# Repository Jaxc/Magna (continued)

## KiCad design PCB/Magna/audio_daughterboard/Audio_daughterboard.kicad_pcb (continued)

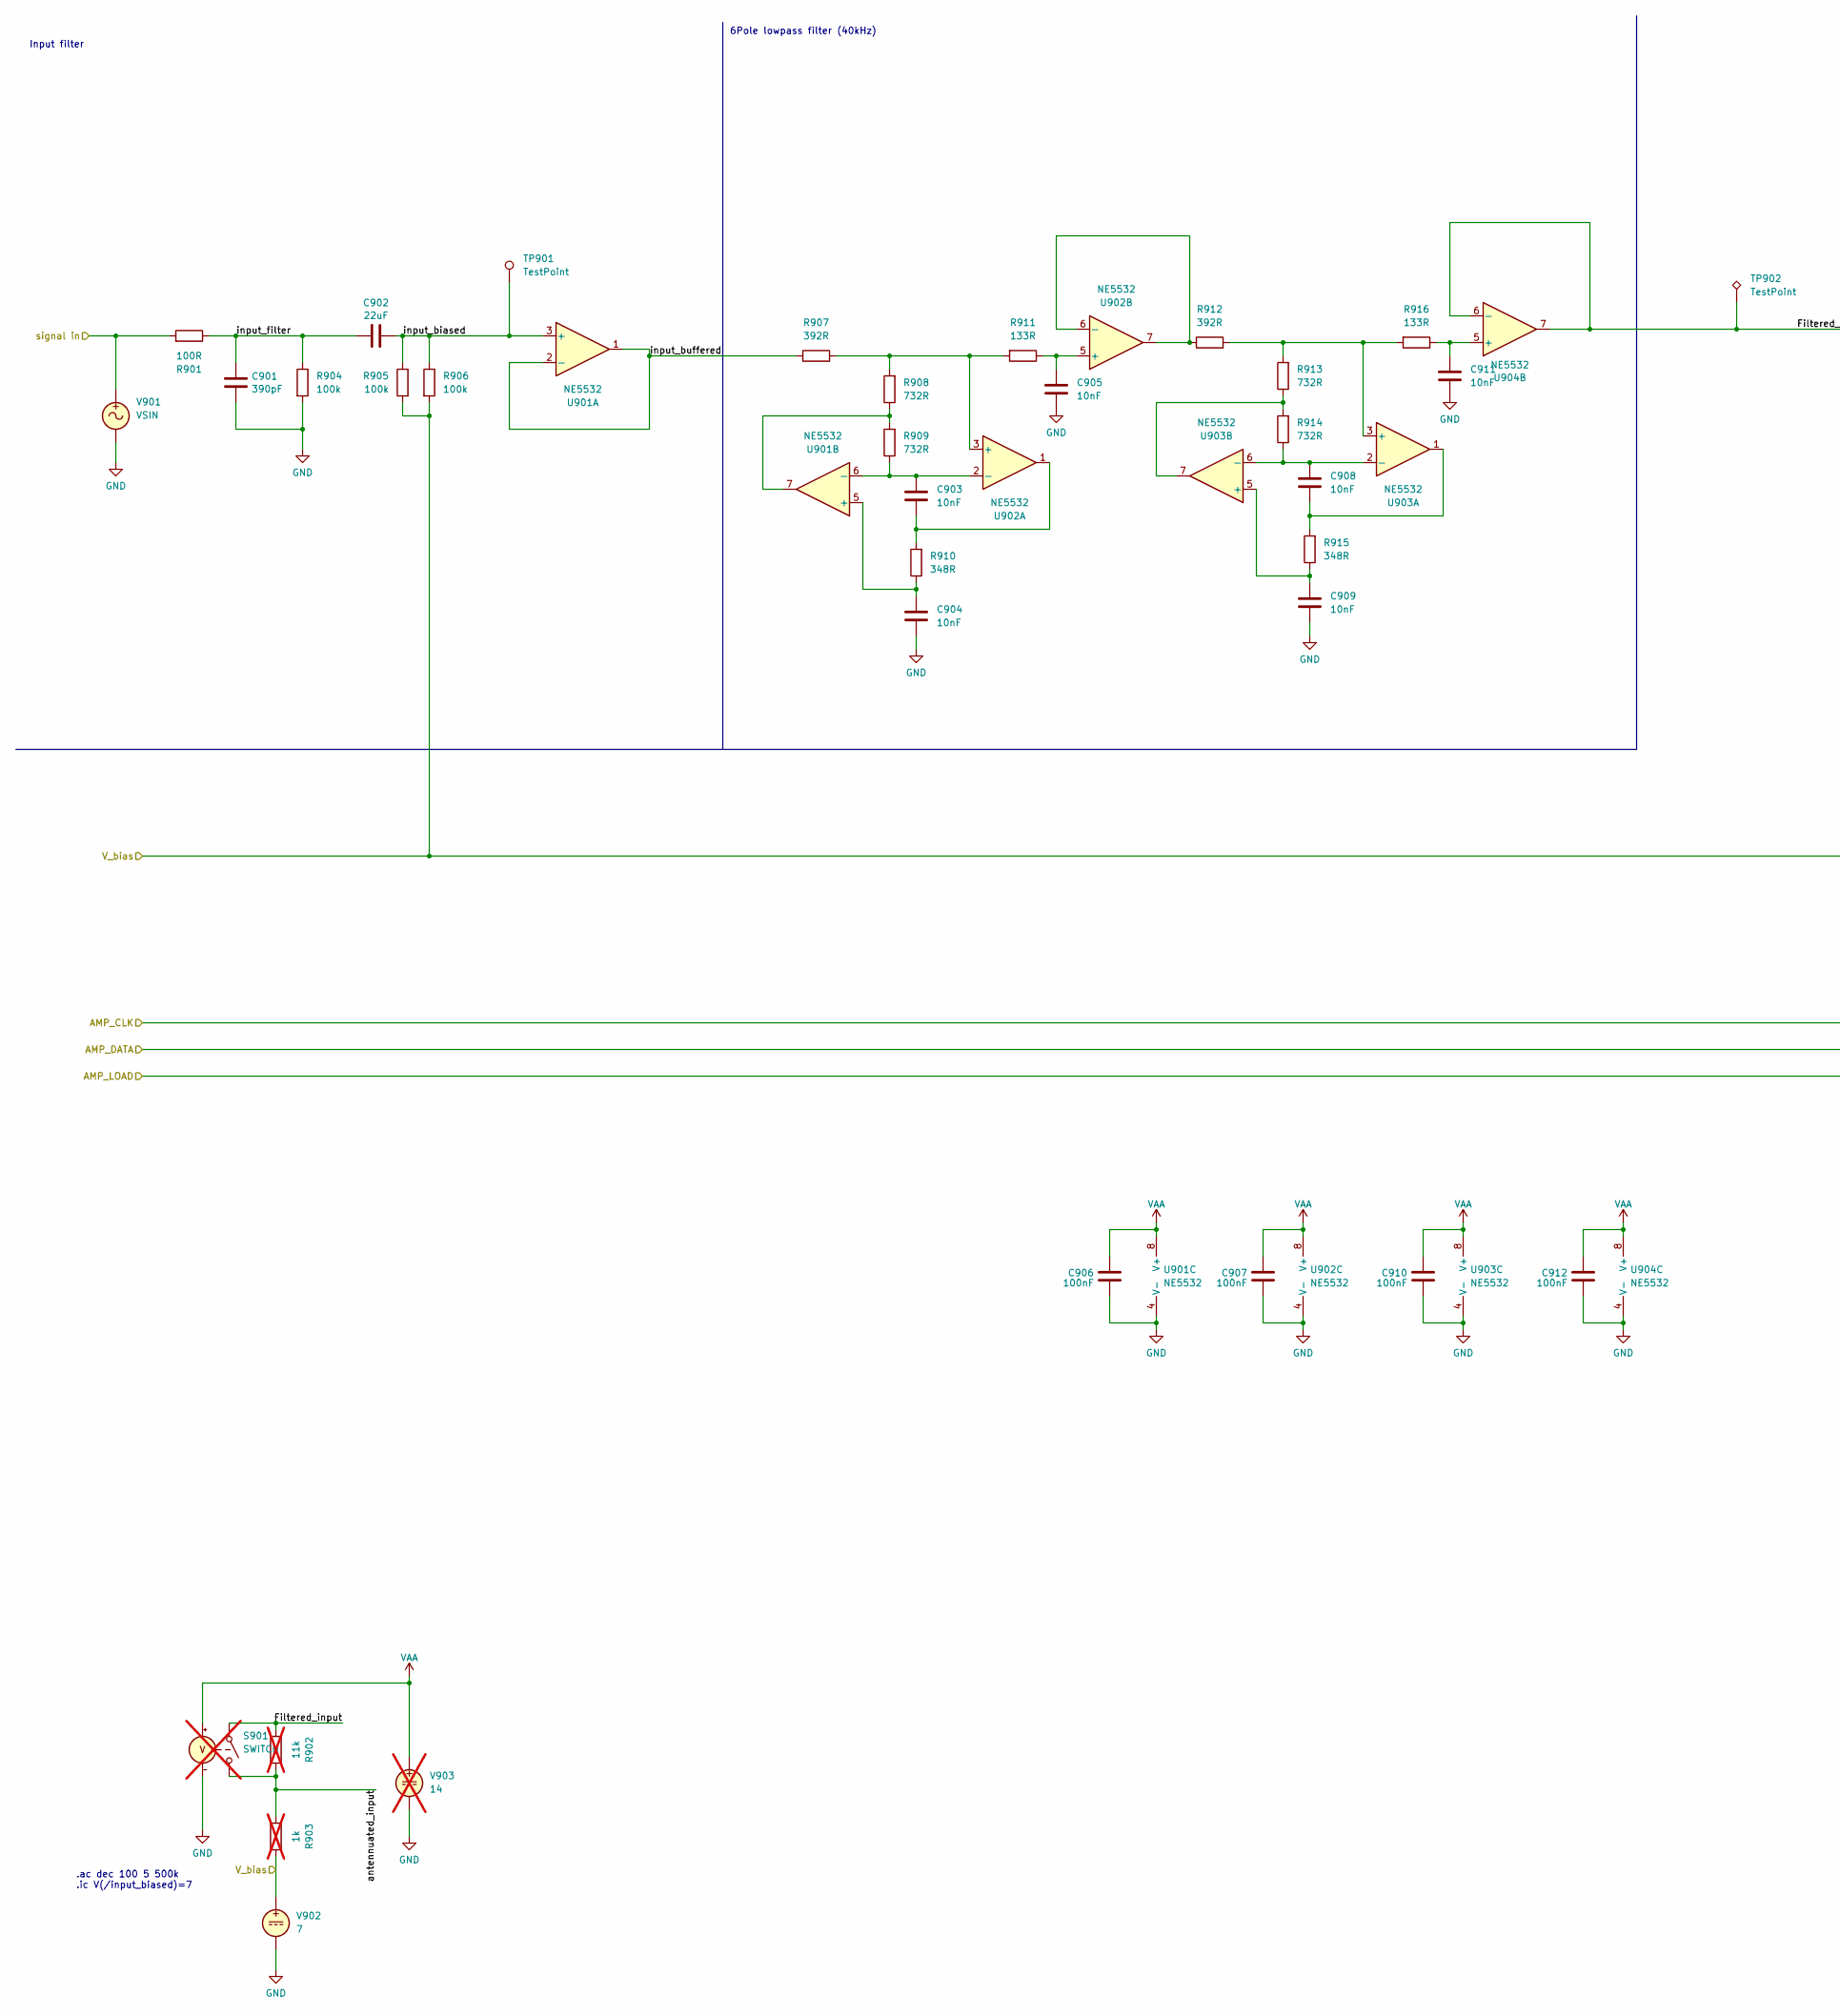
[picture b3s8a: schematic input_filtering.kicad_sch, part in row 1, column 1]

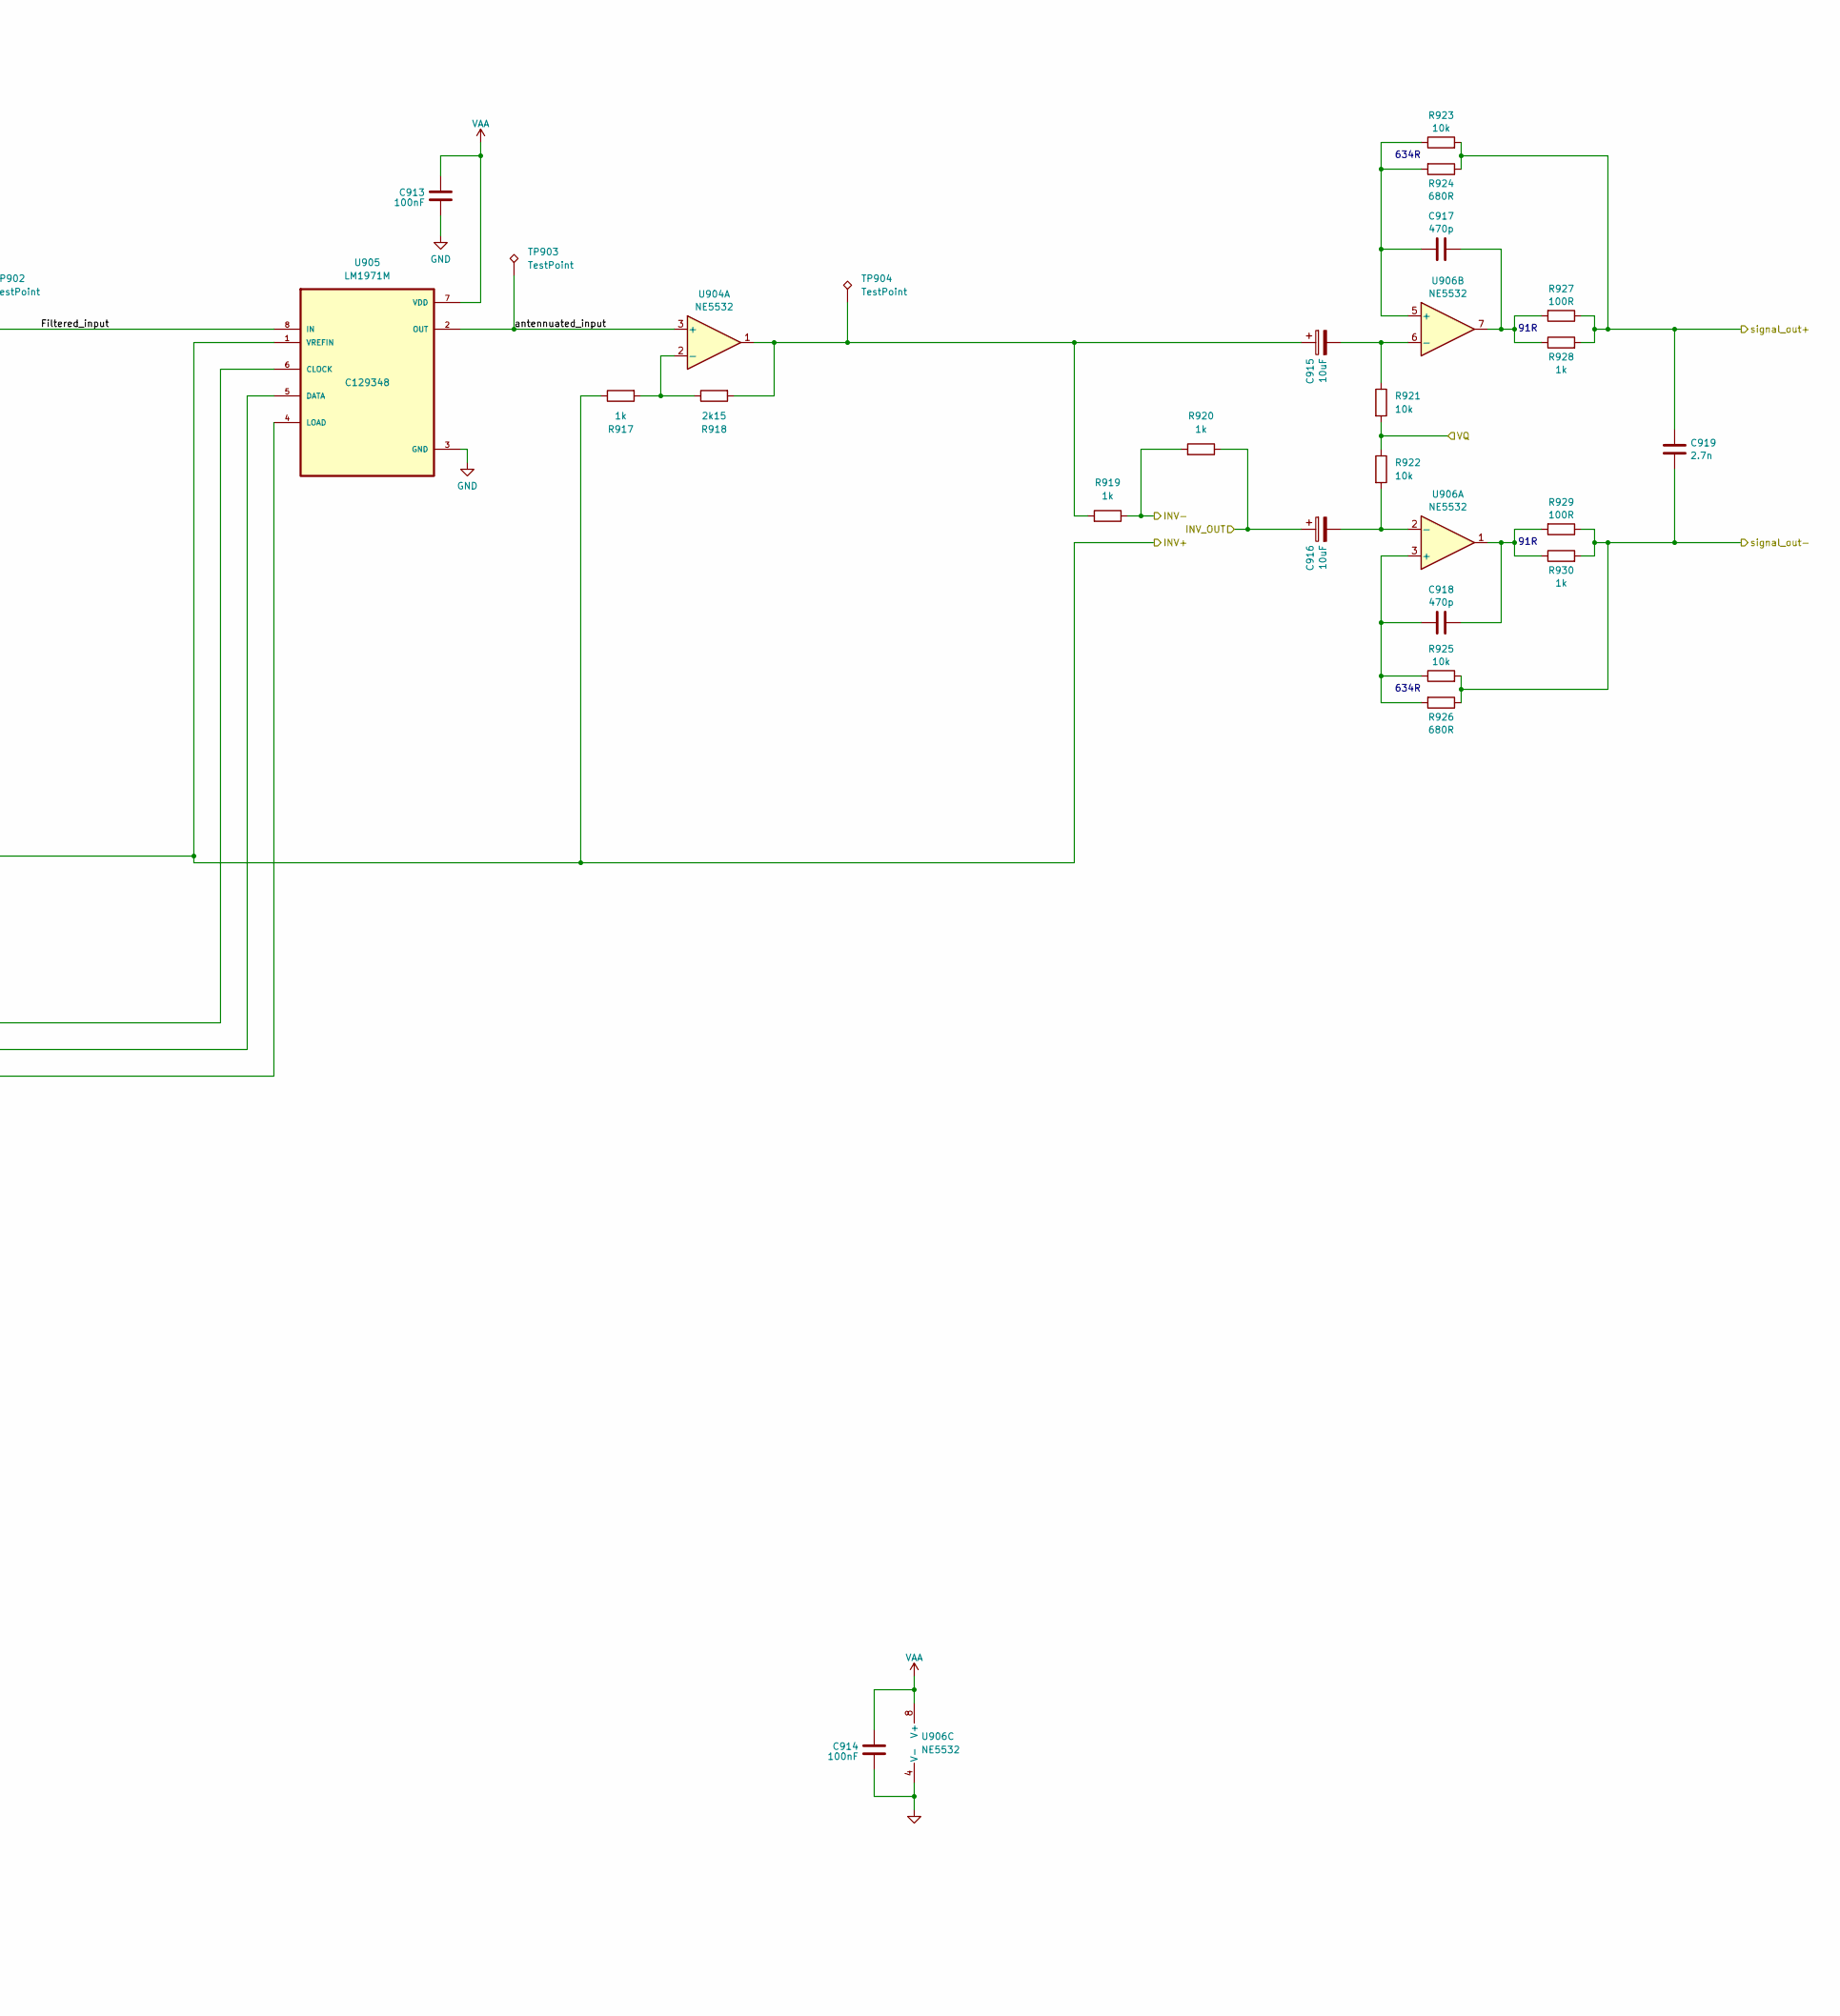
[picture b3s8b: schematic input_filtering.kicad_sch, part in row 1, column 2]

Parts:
C901: 390pF; C_0603_1608Metric; LCSC C472793
C902: 22uF; CP_Elec_6.3x5.4; LCSC C2164172
C903, C904, C905, C908, C909, C911: 10nF; C_0603_1608Metric; LCSC C84709
C906, C907, C910, C912, C913: 100nF; C_0603_1608Metric; Voltage 50V; LCSC C14663
C914: 100nF; C_0603_1608Metric; LCSC C14663
C915, C916: 10uF; CP_Elec_4x5.8; LCSC C2163094
C917, C918: 470p; C_0603_1608Metric; LCSC C27694
C919: 2.7n; C_0603_1608Metric; LCSC C77034
R901, R927, R929: 100R; R_0603_1608Metric; LCSC C122970
R902: 11k; not fitted
R903: 1k; not fitted
R904, R905, R906: 100k; R_0603_1608Metric; LCSC C25803
R907, R912: 392R; R_0603_1608Metric; LCSC C861870
R908, R909, R913, R914: 732R; R_0603_1608Metric; LCSC C861547
R910, R915: 348R; R_0603_1608Metric; LCSC C861337
R911, R916: 133R; R_0603_1608Metric; LCSC C861112
R917, R919, R920, R928, R930: 1k; R_0603_1608Metric; LCSC C110776
R918: 2k15; R_0603_1608Metric; LCSC C667562
R921, R922, R923, R925: 10k; R_0603_1608Metric; LCSC C95204
R924, R926: 680R; R_0603_1608Metric; LCSC C2989042
S901: SWITCH; not fitted
TP901: TestPoint; TestPoint_Keystone_5005-5009_Compact
TP902, TP903, TP904: TestPoint; TestPoint_Pad_1.0x1.0mm
U901, U902, U903, U904, U906: NE5532; SOIC-8_3.9x4.9mm_P1.27mm; LCSC C7426
U905: LM1971M; SOIC-8_3.9x4.9mm_P1.27mm; LCSC C129348
V901: VSIN
V902: 7
V903: 14; not fitted

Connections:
/AudioAdc0/AMP_CLK: U905.6 (CLOCK); also elsewhere on the board
/AudioAdc0/AMP_DATA: U905.5 (DATA); also elsewhere on the board
/AudioAdc0/AMP_LOAD: U905.4 (LOAD); also elsewhere on the board
/AudioAdc0/Input Filtering/Filtered_input: TP902.1, U904.6 (-), U904.7, U905.8 (IN)
/AudioAdc0/Input Filtering/INV-: R919.1, R920.2; also elsewhere on the board
/AudioAdc0/Input Filtering/INV_OUT: C916.1, R920.1; also elsewhere on the board
/AudioAdc0/Input Filtering/antennuated_input: TP903.1, U904.3 (+), U905.2 (OUT)
/AudioAdc0/Input Filtering/input_biased: C902.1, R905.1, R906.1, TP901.1, U901.3 (+)
/AudioAdc0/Input Filtering/input_buffered: R907.1, U901.1, U901.2 (-)
/AudioAdc0/Input Filtering/input_filter: C901.2, C902.2, R901.1, R904.1
/AudioAdc0/Input Filtering/signal in: R901.2; also elsewhere on the board
/AudioAdc0/Input Filtering/signal_out+: C919.1, R923.2, R924.1, R927.1, R928.2; also elsewhere on the board
/AudioAdc0/Input Filtering/signal_out-: C919.2, R925.2, R926.1, R929.1, R930.2; also elsewhere on the board
/AudioAdc0/VQ: R921.2, R922.1; also elsewhere on the board
GND: C901.1, C904.2, C905.2, C906.2, C907.2, C909.2, C910.2, C911.2, C912.2, C913.2, C914.2, R904.2, S901.4 (C-), U901.4 (V-), U902.4 (V-), U903.4 (V-), U904.4 (V-), U905.3 (GND), U906.4 (V-), V901.2, V902.2, V903.2; also elsewhere on the board
unnamed: C903.2, R910.2, U902.1
unnamed: C908.2, R915.2, U903.1
unnamed: C915.1, R918.2, R919.2, TP904.1, U904.1
unnamed: C917.2, R927.2, R928.1, U906.7
unnamed: C918.2, R929.2, R930.1, U906.1
unnamed: R908.1, R909.2, U901.7
unnamed: R913.1, R914.2, U903.7
unnamed: C904.1, R910.1, U901.5 (+)
unnamed: C903.1, R909.1, U901.6 (-), U902.2 (-)
unnamed: R907.2, R908.2, R911.2, U902.3 (+)
unnamed: C905.1, R911.1, U902.5 (+)
unnamed: R912.1, U902.6 (-), U902.7
unnamed: R912.2, R913.2, R916.2, U903.3 (+)
unnamed: C908.1, R914.1, U903.2 (-), U903.6 (-)
unnamed: C909.1, R915.1, U903.5 (+)
unnamed: R917.2, R918.1, U904.2 (-)
unnamed: C911.1, R916.1, U904.5 (+)
unnamed: C918.1, R925.1, R926.2, U906.3 (+)
unnamed: C916.2, R922.2, U906.2 (-)
unnamed: C917.1, R923.1, R924.2, U906.5 (+)
unnamed: C915.2, R921.1, U906.6 (-)
VAA: C906.1, C907.1, C910.1, C912.1, C913.1, C914.1, S901.3 (C+), U901.8 (V+), U902.8 (V+), U903.8 (V+), U904.8 (V+), U905.7 (VDD), U906.8 (V+), V903.1; also elsewhere on the board
VAA_BIAS_R: R905.2, R906.2, R917.1, U905.1 (VREFIN); also elsewhere on the board

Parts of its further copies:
C1001, C1101, C1201: 390pF; C_0603_1608Metric; LCSC C472793
C1002, C1102, C1202: 22uF; CP_Elec_6.3x5.4; LCSC C2164172
C1003, C1004, C1005, C1008, C1009, C1011, C1103, C1104, C1105, C1108, C1109, C1111, C1203, C1204, C1205, C1208, C1209, C1211: 10nF; C_0603_1608Metric; LCSC C84709
C1006, C1007, C1010, C1012, C1013, C1106, C1107, C1110, C1112, C1113, C1206, C1207, C1210, C1212, C1213: 100nF; C_0603_1608Metric; Voltage 50V; LCSC C14663
C1014, C1114, C1214: 100nF; C_0603_1608Metric; LCSC C14663
C1015, C1016, C1115, C1116, C1215, C1216: 10uF; CP_Elec_4x5.8; LCSC C2163094
C1017, C1018, C1117, C1118, C1217, C1218: 470p; C_0603_1608Metric; LCSC C27694
C1019, C1119, C1219: 2.7n; C_0603_1608Metric; LCSC C77034
R1001, R1027, R1029, R1101, R1127, R1129, R1201, R1227, R1229: 100R; R_0603_1608Metric; LCSC C122970
R1004, R1005, R1006, R1104, R1105, R1106, R1204, R1205, R1206: 100k; R_0603_1608Metric; LCSC C25803
R1007, R1012, R1107, R1112, R1207, R1212: 392R; R_0603_1608Metric; LCSC C861870
R1008, R1009, R1013, R1014, R1108, R1109, R1113, R1114, R1208, R1209, R1213, R1214: 732R; R_0603_1608Metric; LCSC C861547
R1010, R1015, R1110, R1115, R1210, R1215: 348R; R_0603_1608Metric; LCSC C861337
R1011, R1016, R1111, R1116, R1211, R1216: 133R; R_0603_1608Metric; LCSC C861112
R1017, R1019, R1020, R1028, R1030, R1117, R1119, R1120, R1128, R1130, R1217, R1219, R1220, R1228, R1230: 1k; R_0603_1608Metric; LCSC C110776
R1018, R1118, R1218: 2k15; R_0603_1608Metric; LCSC C667562
R1021, R1022, R1023, R1025, R1121, R1122, R1123, R1125, R1221, R1222, R1223, R1225: 10k; R_0603_1608Metric; LCSC C95204
R1024, R1026, R1124, R1126, R1224, R1226: 680R; R_0603_1608Metric; LCSC C2989042
TP1001, TP1101, TP1201: TestPoint; TestPoint_Keystone_5005-5009_Compact
TP1002, TP1003, TP1004, TP1102, TP1103, TP1104, TP1202, TP1203, TP1204: TestPoint; TestPoint_Pad_1.0x1.0mm
U1001, U1002, U1003, U1004, U1006, U1101, U1102, U1103, U1104, U1106, U1201, U1202, U1203, U1204, U1206: NE5532; SOIC-8_3.9x4.9mm_P1.27mm; LCSC C7426
U1005, U1105, U1205: LM1971M; SOIC-8_3.9x4.9mm_P1.27mm; LCSC C129348

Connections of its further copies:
/AudioAdc0/AMP_CLK: U1005.6 (CLOCK), U1105.6 (CLOCK), U1205.6 (CLOCK); also elsewhere on the board
/AudioAdc0/AMP_DATA: U1005.5 (DATA), U1105.5 (DATA), U1205.5 (DATA); also elsewhere on the board
/AudioAdc0/AMP_LOAD: U1005.4 (LOAD); also elsewhere on the board
/AudioAdc0/Input Filtering1/Filtered_input: TP1002.1, U1004.6 (-), U1004.7, U1005.8 (IN)
/AudioAdc0/Input Filtering1/INV-: R1019.1, R1020.2; also elsewhere on the board
/AudioAdc0/Input Filtering1/INV_OUT: C1016.1, R1020.1; also elsewhere on the board
/AudioAdc0/Input Filtering1/antennuated_input: TP1003.1, U1004.3 (+), U1005.2 (OUT)
/AudioAdc0/Input Filtering1/input_biased: C1002.1, R1005.1, R1006.1, TP1001.1, U1001.3 (+)
/AudioAdc0/Input Filtering1/input_buffered: R1007.1, U1001.1, U1001.2 (-)
/AudioAdc0/Input Filtering1/input_filter: C1001.2, C1002.2, R1001.1, R1004.1
/AudioAdc0/Input Filtering1/signal in: R1001.2; also elsewhere on the board
/AudioAdc0/Input Filtering1/signal_out+: C1019.1, R1023.2, R1024.1, R1027.1, R1028.2; also elsewhere on the board
/AudioAdc0/Input Filtering1/signal_out-: C1019.2, R1025.2, R1026.1, R1029.1, R1030.2; also elsewhere on the board
/AudioAdc0/VQ: R1021.2, R1022.1; also elsewhere on the board
/AudioAdc1/AMP_LOAD: U1105.4 (LOAD), U1205.4 (LOAD); also elsewhere on the board
/AudioAdc1/Input Filtering1/Filtered_input: TP1102.1, U1104.6 (-), U1104.7, U1105.8 (IN)
/AudioAdc1/Input Filtering1/INV-: R1119.1, R1120.2; also elsewhere on the board
/AudioAdc1/Input Filtering1/INV_OUT: C1116.1, R1120.1; also elsewhere on the board
/AudioAdc1/Input Filtering1/antennuated_input: TP1103.1, U1104.3 (+), U1105.2 (OUT)
/AudioAdc1/Input Filtering1/input_biased: C1102.1, R1105.1, R1106.1, TP1101.1, U1101.3 (+)
/AudioAdc1/Input Filtering1/input_buffered: R1107.1, U1101.1, U1101.2 (-)
/AudioAdc1/Input Filtering1/input_filter: C1101.2, C1102.2, R1101.1, R1104.1
/AudioAdc1/Input Filtering1/signal in: R1101.2; also elsewhere on the board
/AudioAdc1/Input Filtering1/signal_out+: C1119.1, R1123.2, R1124.1, R1127.1, R1128.2; also elsewhere on the board
/AudioAdc1/Input Filtering1/signal_out-: C1119.2, R1125.2, R1126.1, R1129.1, R1130.2; also elsewhere on the board
/AudioAdc1/Input Filtering/Filtered_input: TP1202.1, U1204.6 (-), U1204.7, U1205.8 (IN)
/AudioAdc1/Input Filtering/INV-: R1219.1, R1220.2; also elsewhere on the board
/AudioAdc1/Input Filtering/INV_OUT: C1216.1, R1220.1; also elsewhere on the board
/AudioAdc1/Input Filtering/antennuated_input: TP1203.1, U1204.3 (+), U1205.2 (OUT)
/AudioAdc1/Input Filtering/input_biased: C1202.1, R1205.1, R1206.1, TP1201.1, U1201.3 (+)
/AudioAdc1/Input Filtering/input_buffered: R1207.1, U1201.1, U1201.2 (-)
/AudioAdc1/Input Filtering/input_filter: C1201.2, C1202.2, R1201.1, R1204.1
/AudioAdc1/Input Filtering/signal in: R1201.2; also elsewhere on the board
/AudioAdc1/Input Filtering/signal_out+: C1219.1, R1223.2, R1224.1, R1227.1, R1228.2; also elsewhere on the board
/AudioAdc1/Input Filtering/signal_out-: C1219.2, R1225.2, R1226.1, R1229.1, R1230.2; also elsewhere on the board
/AudioAdc1/VQ: R1121.2, R1122.1, R1221.2, R1222.1; also elsewhere on the board
GND: C1001.1, C1004.2, C1005.2, C1006.2, C1007.2, C1009.2, C1010.2, C1011.2, C1012.2, C1013.2, C1014.2, C1101.1, C1104.2, C1105.2, C1106.2, C1107.2, C1109.2, C1110.2, C1111.2, C1112.2, C1113.2, C1114.2, C1201.1, C1204.2, C1205.2, C1206.2, C1207.2, C1209.2, C1210.2, C1211.2, C1212.2, C1213.2, C1214.2, R1004.2, R1104.2, R1204.2, U1001.4 (V-), U1002.4 (V-), U1003.4 (V-), U1004.4 (V-), U1005.3 (GND), U1006.4 (V-), U1101.4 (V-), U1102.4 (V-), U1103.4 (V-), U1104.4 (V-), U1105.3 (GND), U1106.4 (V-), U1201.4 (V-), U1202.4 (V-), U1203.4 (V-), U1204.4 (V-), U1205.3 (GND), U1206.4 (V-); also elsewhere on the board
unnamed: C1003.2, R1010.2, U1002.1
unnamed: C1008.2, R1015.2, U1003.1
unnamed: C1015.1, R1018.2, R1019.2, TP1004.1, U1004.1
unnamed: C1017.2, R1027.2, R1028.1, U1006.7
unnamed: C1018.2, R1029.2, R1030.1, U1006.1
unnamed: C1103.2, R1110.2, U1102.1
unnamed: C1108.2, R1115.2, U1103.1
unnamed: C1115.1, R1118.2, R1119.2, TP1104.1, U1104.1
unnamed: C1117.2, R1127.2, R1128.1, U1106.7
unnamed: C1118.2, R1129.2, R1130.1, U1106.1
unnamed: C1203.2, R1210.2, U1202.1
unnamed: C1208.2, R1215.2, U1203.1
unnamed: C1215.1, R1218.2, R1219.2, TP1204.1, U1204.1
unnamed: C1217.2, R1227.2, R1228.1, U1206.7
unnamed: C1218.2, R1229.2, R1230.1, U1206.1
unnamed: R1008.1, R1009.2, U1001.7
unnamed: R1013.1, R1014.2, U1003.7
unnamed: R1108.1, R1109.2, U1101.7
unnamed: R1113.1, R1114.2, U1103.7
unnamed: R1208.1, R1209.2, U1201.7
unnamed: R1213.1, R1214.2, U1203.7
unnamed: C1004.1, R1010.1, U1001.5 (+)
unnamed: C1003.1, R1009.1, U1001.6 (-), U1002.2 (-)
unnamed: R1007.2, R1008.2, R1011.2, U1002.3 (+)
unnamed: C1005.1, R1011.1, U1002.5 (+)
unnamed: R1012.1, U1002.6 (-), U1002.7
unnamed: R1012.2, R1013.2, R1016.2, U1003.3 (+)
unnamed: C1008.1, R1014.1, U1003.2 (-), U1003.6 (-)
unnamed: C1009.1, R1015.1, U1003.5 (+)
unnamed: R1017.2, R1018.1, U1004.2 (-)
unnamed: C1011.1, R1016.1, U1004.5 (+)
unnamed: C1018.1, R1025.1, R1026.2, U1006.3 (+)
unnamed: C1016.2, R1022.2, U1006.2 (-)
unnamed: C1017.1, R1023.1, R1024.2, U1006.5 (+)
unnamed: C1015.2, R1021.1, U1006.6 (-)
unnamed: C1104.1, R1110.1, U1101.5 (+)
unnamed: C1103.1, R1109.1, U1101.6 (-), U1102.2 (-)
unnamed: R1107.2, R1108.2, R1111.2, U1102.3 (+)
unnamed: C1105.1, R1111.1, U1102.5 (+)
unnamed: R1112.1, U1102.6 (-), U1102.7
unnamed: R1112.2, R1113.2, R1116.2, U1103.3 (+)
unnamed: C1108.1, R1114.1, U1103.2 (-), U1103.6 (-)
unnamed: C1109.1, R1115.1, U1103.5 (+)
unnamed: R1117.2, R1118.1, U1104.2 (-)
unnamed: C1111.1, R1116.1, U1104.5 (+)
unnamed: C1118.1, R1125.1, R1126.2, U1106.3 (+)
unnamed: C1116.2, R1122.2, U1106.2 (-)
unnamed: C1117.1, R1123.1, R1124.2, U1106.5 (+)
unnamed: C1115.2, R1121.1, U1106.6 (-)
unnamed: C1204.1, R1210.1, U1201.5 (+)
unnamed: C1203.1, R1209.1, U1201.6 (-), U1202.2 (-)
unnamed: R1207.2, R1208.2, R1211.2, U1202.3 (+)
unnamed: C1205.1, R1211.1, U1202.5 (+)
unnamed: R1212.1, U1202.6 (-), U1202.7
unnamed: R1212.2, R1213.2, R1216.2, U1203.3 (+)
unnamed: C1208.1, R1214.1, U1203.2 (-), U1203.6 (-)
unnamed: C1209.1, R1215.1, U1203.5 (+)
unnamed: R1217.2, R1218.1, U1204.2 (-)
unnamed: C1211.1, R1216.1, U1204.5 (+)
unnamed: C1218.1, R1225.1, R1226.2, U1206.3 (+)
unnamed: C1216.2, R1222.2, U1206.2 (-)
unnamed: C1217.1, R1223.1, R1224.2, U1206.5 (+)
unnamed: C1215.2, R1221.1, U1206.6 (-)
VAA: C1006.1, C1007.1, C1010.1, C1012.1, C1013.1, C1014.1, C1106.1, C1107.1, C1110.1, C1112.1, C1113.1, C1114.1, C1206.1, C1207.1, C1210.1, C1212.1, C1213.1, C1214.1, U1001.8 (V+), U1002.8 (V+), U1003.8 (V+), U1004.8 (V+), U1005.7 (VDD), U1006.8 (V+), U1101.8 (V+), U1102.8 (V+), U1103.8 (V+), U1104.8 (V+), U1105.7 (VDD), U1106.8 (V+), U1201.8 (V+), U1202.8 (V+), U1203.8 (V+), U1204.8 (V+), U1205.7 (VDD), U1206.8 (V+); also elsewhere on the board
VAA_BIAS_L: R1005.2, R1006.2, R1017.1, R1105.2, R1106.2, R1117.1, U1005.1 (VREFIN), U1105.1 (VREFIN); also elsewhere on the board
VAA_BIAS_R: R1205.2, R1206.2, R1217.1, U1205.1 (VREFIN); also elsewhere on the board

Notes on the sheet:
634R
91R
6Pole lowpass filter (40kHz)
.ac dec 100 5 500k .ic V(/input_biased)=7
Input filter

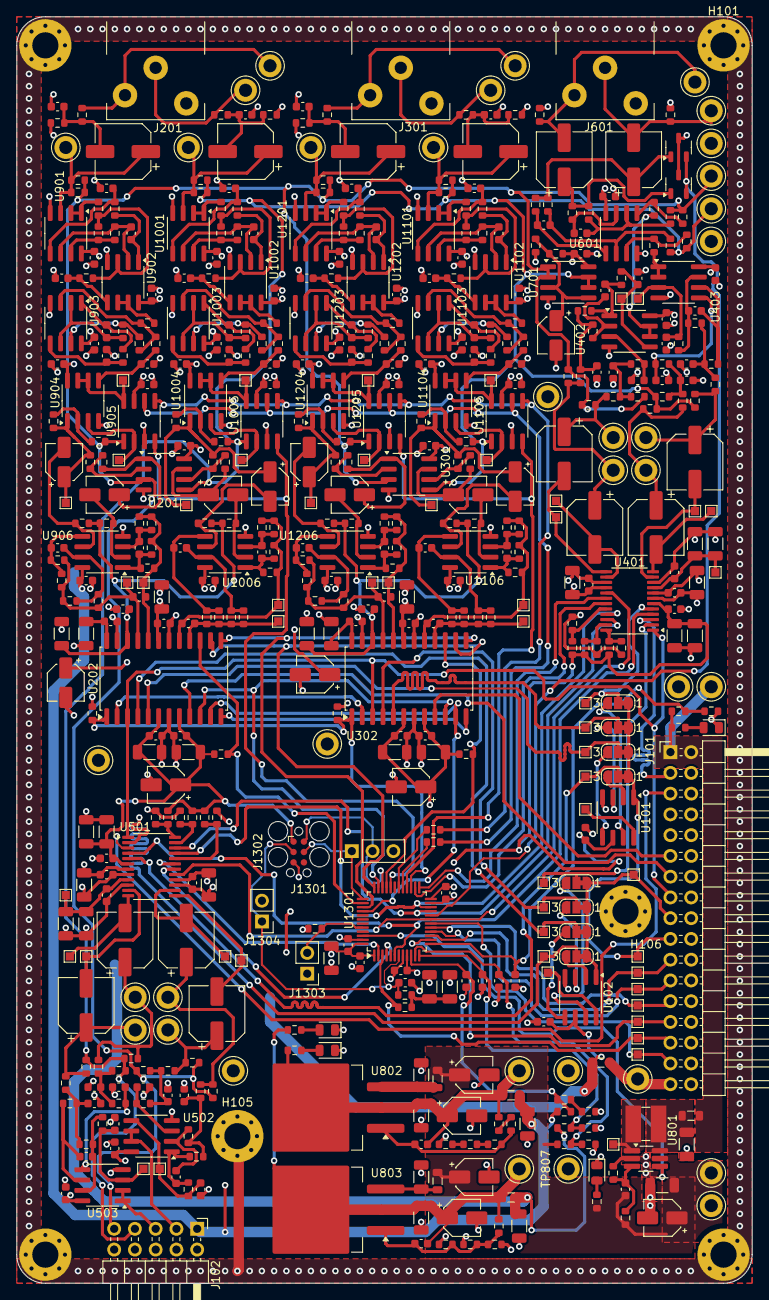
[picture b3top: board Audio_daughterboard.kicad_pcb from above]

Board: 4 copper layers, 90.0 x 155.0 mm, 564 parts (0 on the bottom side), 283 nets.

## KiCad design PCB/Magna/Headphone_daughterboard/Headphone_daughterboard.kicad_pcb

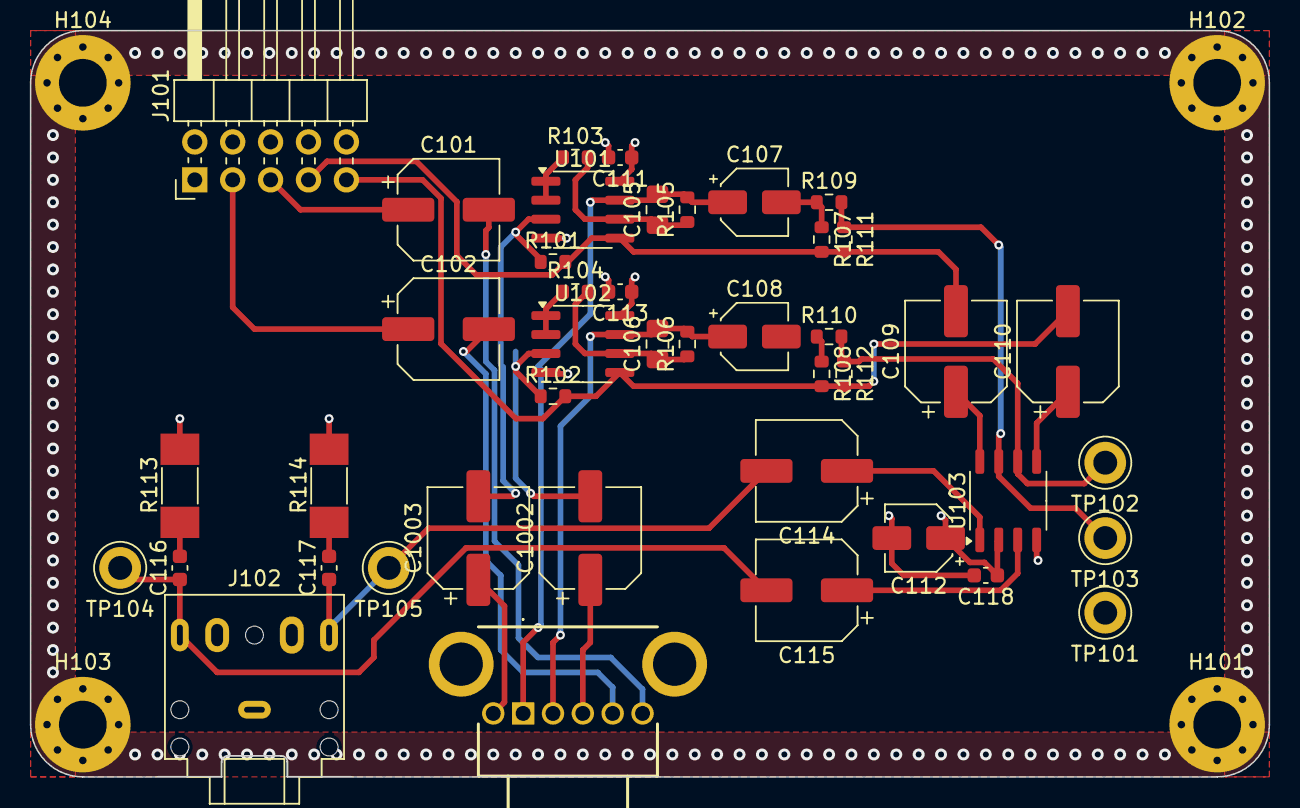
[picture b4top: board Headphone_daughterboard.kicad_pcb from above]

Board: 4 copper layers, 83.0 x 50.0 mm, 47 parts (0 on the bottom side), 31 nets.

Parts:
C101, C102, C109, C110, C114, C115: 100u; CP_Elec_6.3x7.7
C105, C106: 100pF; C_0805_2012Metric_Pad1.18x1.45mm_HandSolder
C107, C108: 220uF; CP_Elec_4x5.8
C111, C113, C116, C117, C118: 100nF; C_0603_1608Metric
C112: 10uF; CP_Elec_4x5.8
C1002, C1003: 22uF; CP_Elec_6.3x5.4
H101, H102, H103, H104: MountingHole_Pad; MountingHole_3.2mm_M3_Pad_Via
J101: Conn_02x05_Odd_Even; PinHeader_2x05_P2.54mm_Horizontal
J102: AudioJack3; Jack_3.5mm_CUI_SJ1-3525N_Horizontal
R101, R102, R107, R108: 22k; R_0603_1608Metric
R103, R104, R105, R106: 680R; R_0603_1608Metric
R109, R110: 100R; R_0603_1608Metric
R111, R112: 10k; R_0603_1608Metric
R113, R114: 4R7; R_MELF_MMB-0207
RV101: 10k; Potentiometer_Bourns_PTV112-1417-AA103
TP101, TP102, TP103, TP104, TP105: TestPoint; TestPoint_Keystone_5005-5009_Compact
U101, U102: NE5532; SOIC-8_3.9x4.9mm_P1.27mm
U103: TDA2822D; SOP-8_3.9x4.9mm_P1.27mm

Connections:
/AudioInL: C101.1, J101.5
/AudioInR: C102.1, J101.3
/VAA_BIAS_L: C109.2, J101.7, R101.2, R107.2, R111.2, U101.5 (+)
/VAA_BIAS_R: C110.2, J101.9, R102.2, R108.2, R112.2, U102.5 (+)
GND: C111.2, C112.2, C113.2, C118.2, J101.2, J101.4, J101.6, J101.8, J101.10, J102.S, R113.2, R114.2, RV101.MP, TP101.1, U101.4 (V-), U102.4 (V-), U103.4 (GND)
unnamed: C101.2, RV101.3
unnamed: C102.2, RV101.6
unnamed: C105.2, C107.1, R105.2, RV101.1, U101.7
unnamed: C106.2, C108.1, R106.2, RV101.4, U102.7
unnamed: C107.2, R107.1, R109.1
unnamed: C108.2, R108.1, R110.1
unnamed: C114.2, C117.1, J102.T, TP105.1
unnamed: C115.2, C116.1, J102.R, TP104.1
unnamed: C116.2, R113.1
unnamed: C117.2, R114.1
unnamed: C1002.1, RV101.5
unnamed: C1003.1, RV101.2
unnamed: C1003.2, R101.1, U101.3 (+)
unnamed: R103.1, U101.1, U101.2 (-)
unnamed: C105.1, R103.2, R105.1, U101.6 (-)
unnamed: C1002.2, R102.1, U102.3 (+)
unnamed: R104.1, U102.1, U102.2 (-)
unnamed: C106.1, R104.2, R106.1, U102.6 (-)
unnamed: C109.1, U103.8 (Input1+)
unnamed: R109.2, R111.1, TP103.1, U103.7 (Input1-)
unnamed: C110.1, U103.5 (Input2+)
unnamed: R110.2, R112.1, TP102.1, U103.6 (Input2-)
unnamed: C114.1, U103.1 (OUTPUT1)
unnamed: C115.1, U103.3 (OUTPUT2)
SHIELD: H101.1, H102.1, H103.1, H104.1
VAA: C111.1, C112.1, C113.1, C118.1, J101.1, U101.8 (V+), U102.8 (V+), U103.2 (VCC)

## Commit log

2020-03-26 Initial code
2020-03-28 setup timer configuation for automatic mux readout
    Tim1 and Tim2 are set up to loop through 3 addressing
    to enable for analogue sampling from muxes. ADC is
    connected through TRGO interface to sync sampling
2020-03-28 Add SAI and USB interfaces
2020-03-28 Update HAL version
2020-03-29 Backup before i go crazy on the code
2020-03-29 fix clocks and usb
2020-03-29 Update the USB descriptor to enable audio in/out
2020-03-31 Add various fixes to get USB working properly
    Still no luck
2020-04-01 Add .circleci/config.yml
2020-04-01 Add static code tools
2020-04-01 Fix CI config
2020-04-01 Add sonar config
2020-04-04 Add drivers for dac codec
2020-04-05 make USB work okay
2020-04-05 Add queue functionality as a basic RT system
2020-04-06 Fix some of the audio issues
    It still sounds bad
2020-04-06 Continue to fix I2S issues, but no working solution
    I2S DMA triggers twice as fast as suspected.
2020-04-07 Add support for new codec
2020-04-10 Add guards to select codec
2020-04-11 add functioning USB audio
2020-04-18 Add FMC support for SDRAM and other fixes
2020-08-05 Backup before linux reinstall
2024-01-24 Add PCB design files
2024-01-28 Add diagrams of HW system
2024-01-30 Update analogue frontend and add potentiometer interface
2024-02-08 Update USB schematic with ESD protection and extra port
2024-02-09 Update MCU schematic
    Should be ready for review
2024-02-09 Add final touched to all schematics
2024-02-12 Remove fp-info-cache
2024-02-12 Remove all ERC in schematics
2024-02-12 Update capacitors to parts in JLC library
2024-02-13 Select parts for all components
2024-02-14 Add even more component footprints and partnumbers
2024-02-14 Change processor to STM32F765
2024-02-14 Split schematic to several projects
    To allow for several boards to be done a kicad project
    is needed for each
2024-02-15 Add a lot on the IO PCB
    Also some schematic changes to accomodate issues found
    when routing
2024-02-16 [PATCH] Fix VDDA and GND flip on U101-102-103
2024-02-17 Route most of io daughterboard
2024-02-18 Add more routing to IO Daugherboard
2024-02-18 Fix DRC erros and warnings
2024-02-18 Fix DRC issues from rounded tracks
2024-02-18 Make rounded lines look nicer for the analogue part
2024-02-19 Make rounded traces look better for digital signals
2024-02-19 revert unchanged files
2024-02-19 Make rounded traces look better for digital signals (#2)
2024-02-19 Make IO daughterboard production ready
2024-02-20 Fix CI runs
2024-02-20 More fix
2024-02-20 change machine tag
2024-02-20 Change image for CircleCI
2024-02-20 Update Project Key for Sonarcloud
2024-02-20 Remove Sudo again
2024-02-20 Change image for CI builds
2024-02-20 Update buildwrapper
2024-02-20 update sonarcloud orb
2024-02-20 Change CI image
2024-02-20 Add sudo again
2024-02-20 Update sonarqube orb version
2024-02-20 Add sudo to apt commands
2024-02-20 Update project keys
2024-02-20 Fix CI compilation and analysis of code (#3)
2024-02-20 -Add MIDI electrical and TRS spec -Add newer optocoupler datasheet
2024-02-20 -Add LCSC numbers -Fix annotation and presentation -update .gitignore
2024-02-20 -Add MIDI alternative design -substitute CMOS optocoupler TLP2361. This is faster, smaller, cheaper and does not need pull-up resistor to VDD. -add RX/TX activity monitor LEDs for debugging -flip mid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
2024-02-20 -Add MIDI pwl stream generator script -Add LTSpice sim for RX/TX LED indicators (uses the generated pwl file as input) -Update R value for filter in schematic after simulations
2024-02-20 substitute MIDI sheets and click save
2024-02-20 Change all capacitors to 22uF
2024-02-20 Add MIDI alternative design (#1)
    * -Add MIDI electrical and TRS spec
    -Add newer optocoupler datasheet
    * -Add MIDI alternative design
    -substitute CMOS optocoupler TLP2361. This is faster, smaller, cheaper and does not need pull-up resistor to VDD.
    -add RX/TX activity monitor LEDs for debugging
    -flip midi_in+ and midi_in-
2024-02-20 Change all capacitors to 22uF on IO board(#5)
2024-02-21 Resize the IO PCB
2024-02-21 Add board outline for Magna Mainboard
2024-02-21 Add board outline for Magna Mainboard (#7)
2024-02-21 Resize the IO PCB (#6)
2024-02-21 Add MCAD project
2024-02-21 Add MCAD project (#8)
2024-02-21 Change Cue Mix potentiometer to front facing model
2024-02-21 Move VAA circuitry to Analogue daughterboard
2024-02-21 Change Cue Mix potentiometer to front facing model (#10)
2024-02-21 Add outline for Audio Daugherboard
2024-02-21 Change connector to IO board
2024-02-21 Move VAA circuitry to Analogue daughterboard (#11)
2024-02-21 Add outline for Audio Daugherboard (#12)
2024-02-21 Change connector to IO board (#13)
2024-02-22 Update Audio connector pinning
2024-02-22 Add cube project changes
2024-02-22 Update Audio connector pinning (#14)
2024-02-22 Add inital layout for Audio Daughterboard
2024-02-22 Add inital layout for Audio Daughterboard (#15)
2024-02-22 Update connector on ADC board and clean up MCU sheet
2024-02-22 Revert unchanged file
2024-02-22 Update connector on ADC board and clean up MCU sheet (#16)
2024-02-22 Change components on Main Board to use more of the same part#
2024-02-22 Change components on Main Board to use more of the same part# (#17)
2024-02-22 Update datasheet for optocoupler
2024-02-22 Update datasheet for optocoupler (#18)
2024-02-22 Start of layout for Mainboard PCB
2024-02-23 Change DCDC for 3V and more deisgn of PCB
2024-02-23 Add more traces to the PCB
2024-02-27 More routing
2024-02-28 Add last routing
2024-03-04 Making the routing way nicer
2024-03-11 Finish PCB design and added mounting holes
2024-03-11 Add ULPI matching calculations
2024-03-11 Mainboard layout (#19)
    Also adds mounting holes to IO daughterboard
2024-03-11 Add final edit to Mainboard design
2024-03-11 Add final edit to Mainboard design (#20)
2024-03-22 Start of redesign of Audio board
2024-03-22 Add simulation to all components
2024-03-27 Finish simulations and design of input filtering
2024-07-23 Update some files to KiCad8 and make ready for production
2024-07-23 Change ADC and add MCU for IO control
2024-07-23 Add audio connector schematic
2024-07-23 More small fixes before production
2024-08-07 Update Project to Kicad 8.0 and prepare for production
2024-08-07 Fix some more small issues on IO board
2024-08-07 Even more small fixes on IO board
2024-08-07 Update IO board with a small change in routing
2024-08-07 Fix small aestectic defect in IO board
2024-08-07 Final check for main board
2025-04-06 Update CircleCI image
2025-04-06 Some updates to PCB
    Honestly I cannot remember whats changed
2025-04-06 Update schematics to Kicad 9
2025-04-06 Update audio PCB
    Mainly added simulations to Linedriver and DAC.
    Also fixed some small issues that was found when simulating
2025-04-09 "Finalize" Audio daugherboard
    Finished DAC output filter
    Fixed the whole damn MCU subschematic
    Fixed Linedriver schematic
2025-04-10 "Finalize" Audio daugherboard
    Finished DAC output filter
    Fixed the whole damn MCU subschematic
    Fixed Linedriver schematic
    Added component footprints and LCSC numbers
2025-04-13 Do most of the component placement for audio board
    Just a general layout, things will probably change
    as the routing begins.
2025-04-14 Start layout and routing of Audio Daugherboard
    Also a lot of small changes to everything that became apperant
    when the audio daughterboard was designed. Such as the Headphone
    PCB, which is now separate from the rest of the audio.
2025-04-20 Finished first round of routing for the Audio Daughterboard
2025-08-06 Update Mainboard PCB
    * Added better power ORing
    * Added DRC for length matching
    * Changed out components for cheaper production
    * Removed some optional circuits from BOM for first prototype
2025-08-07 Fix board alignments and mounting holes
2025-08-08 Length match I2S traces on Audioboard
2025-09-03 Commit with small changes for production
    Mainboard and IO board was manufactored with this version
2025-09-03 Update incorrect footprints on mainboard
    For some reason footprints were incorrect on midi part.
    Also 24.576MHz oscillator was incorrect.
2025-09-11 Inital code commit
2025-09-11 Started to add some threads etc
2025-09-11 regenerated with cube, removing unused files
2025-09-11 Added functionality to the different threads
2025-11-02 Move SW to its own folder
2025-11-02 Inital tasks created
2025-11-02 Adding audio process a bit
2025-11-25 Add inital SW for Mainboard
2025-11-27 Fix stack size and memory placements
2025-11-30 add TIM settings for ADC sampling
2025-12-04 More fixes and stuff
2025-12-04 Added missing files
